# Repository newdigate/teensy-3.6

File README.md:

# Teensy 3.6 audio display projects

I'd like to explore whats possible with a teensy 3.6, the sgtl5000 audioboard, and an ILI9341 tft display board;
* https://www.pjrc.com/teensy/index.html
* https://www.pjrc.com/store/teensy3_audio.html
* https://www.pjrc.com/store/display_ili9341.html

I have a little bit of electrical engineering knowledge but I don't have alot of practical experience. I am a software engineer by trade and Im interested in audio applications of the teensy devices; 

I've wired the three components together using breadboard and jumper wires. Although it does work intermittently, the digital i2s audio connection is very fragile and mostly results in heavy digital distorion. I've tried to rule out all the obvious potential faults - swapped teensy mainboards, swapped audioboards, swapped different versions of teensy devices... the problem seems to be with my breadboard, or the jumper wires. I need to check it out with a decent oscilliscope. So I've decided to build a custom PCB. I think this should solve my distortion issue.    

[some things I learned about Fritzing](https://github.com/newdigate/teensy-3.6/tree/master/fritzing)

### About Teensy:
Teensy is an awesome microcontroller development kit from pjrc.com http://www.pjrc.com/teensy/index.html

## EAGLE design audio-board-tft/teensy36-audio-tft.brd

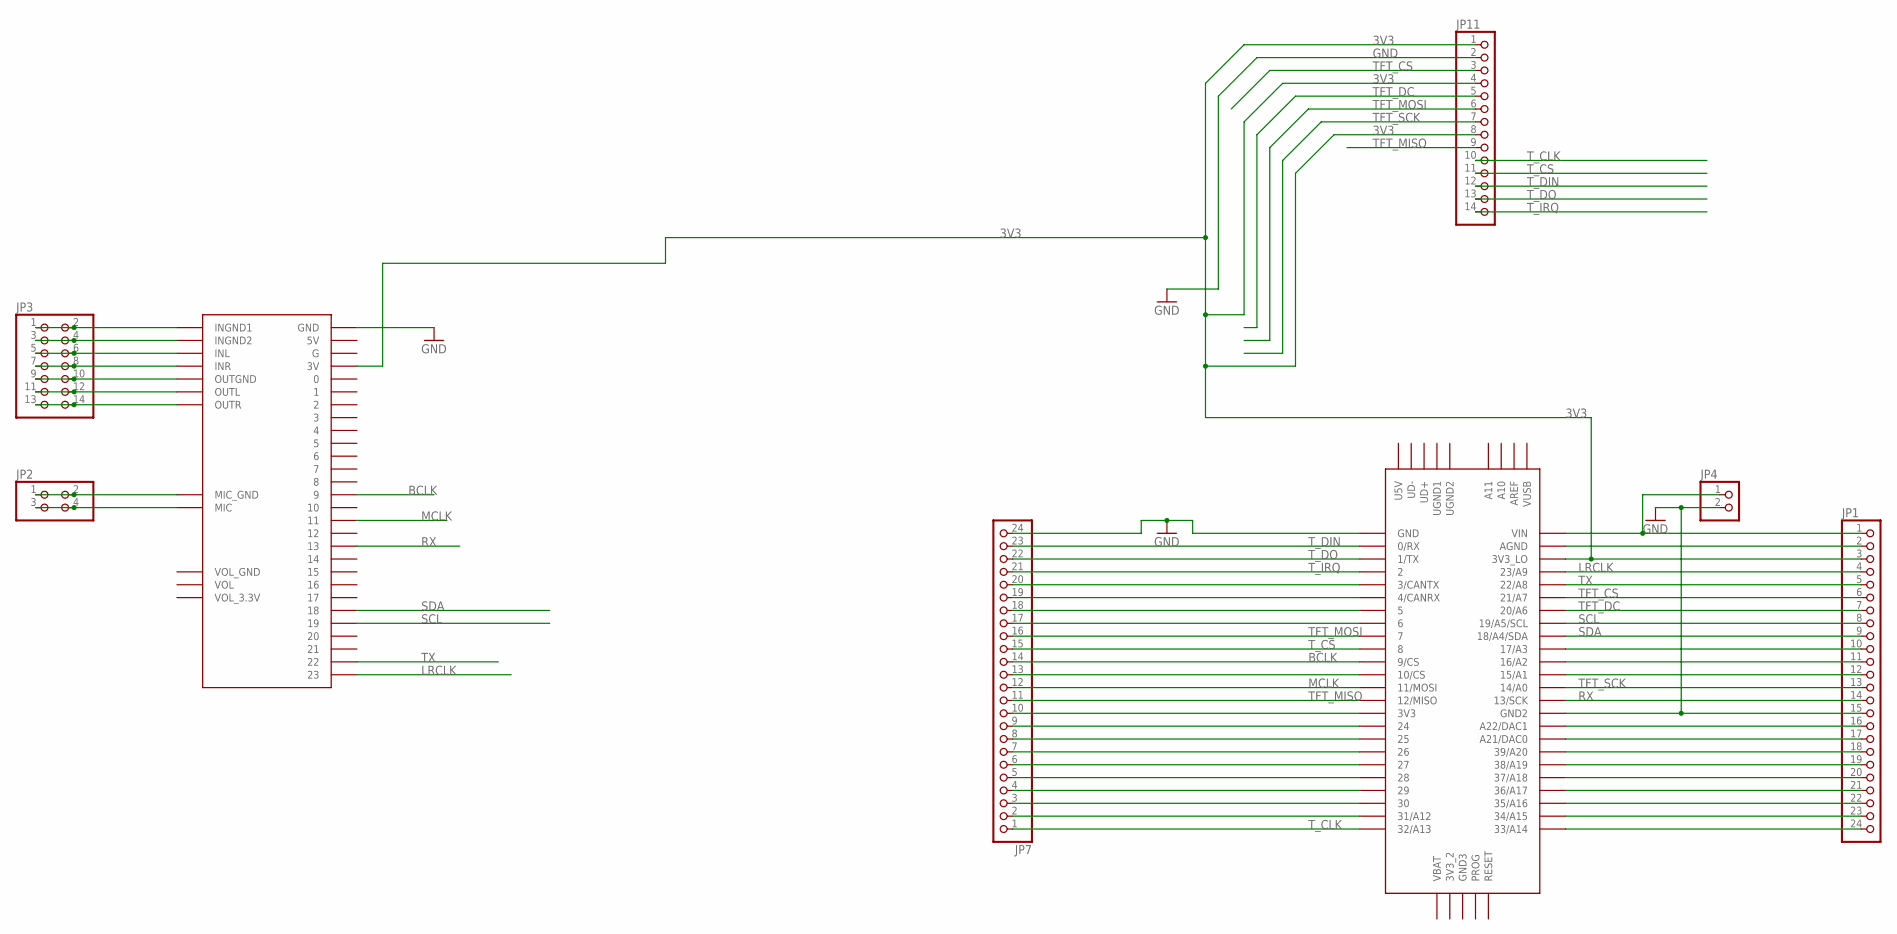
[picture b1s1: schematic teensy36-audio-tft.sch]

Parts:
JP1, JP7: PINHD-1X24; 1X24
JP2: PINHD-2X2; 2X02
JP3: PINHD-2X7; 2X07
JP4: PINHD-1X2; 1X02
JP11: PINHD-1X14; 1X14
U$2: AUDIOSHIELD
U$3: TEENSY_3.5/3.6

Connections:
3V3: JP1.3, JP11.1, JP11.4, JP11.8, U$2.3V, U$3.3V3_LO
BCLK: JP7.14, U$2.9, U$3.9/CS
GND: JP1.15, JP4.2, JP7.24, JP11.2, U$2.GND, U$3.GND, U$3.GND2
LRCLK: JP1.4, U$2.23, U$3.23/A9
MCLK: JP7.12, U$2.11, U$3.11/MOSI
unnamed: JP2.1, JP2.2, U$2.GND_MIC (MIC_GND)
unnamed: JP1.1, JP4.1, U$3.VIN
unnamed: JP7.20, U$3.3/CANTX
unnamed: JP7.19, U$3.4/CANRX
unnamed: JP7.18, U$3.5
unnamed: JP2.3, JP2.4, U$2.MIC
unnamed: JP3.1, JP3.2, U$2.INGND1
unnamed: JP3.3, JP3.4, U$2.INGND2
unnamed: JP3.5, JP3.6, U$2.INL
unnamed: JP3.7, JP3.8, U$2.INR
unnamed: JP3.9, JP3.10, U$2.OUTGND
unnamed: JP3.11, JP3.12, U$2.OUTL
unnamed: JP3.13, JP3.14, U$2.OUTR
unnamed: JP7.17, U$3.6
unnamed: JP7.13, U$3.10/CS
unnamed: JP7.10, U$3.3V3
unnamed: JP7.9, U$3.24
unnamed: JP7.8, U$3.25
unnamed: JP7.7, U$3.26
unnamed: JP7.6, U$3.27
unnamed: JP7.5, U$3.28
unnamed: JP7.4, U$3.29
unnamed: JP7.3, U$3.30
unnamed: JP7.2, U$3.31/A12
unnamed: JP1.2, U$3.AGND
unnamed: JP1.10, U$3.17/A3
unnamed: JP1.11, U$3.16/A2
unnamed: JP1.12, U$3.15/A1
unnamed: JP1.16, U$3.A22/DAC1
unnamed: JP1.17, U$3.21/DAC0 (A21/DAC0)
unnamed: JP1.18, U$3.39/A20
unnamed: JP1.19, U$3.38/A19
unnamed: JP1.20, U$3.37/A18
unnamed: JP1.21, U$3.36/A17
unnamed: JP1.22, U$3.35/A16
unnamed: JP1.23, U$3.34/A15
unnamed: JP1.24, U$3.33/A14
RX: JP1.14, U$2.13, U$3.13/SCK
SCL: JP1.8, U$2.19, U$3.19/A5/SCL
SDA: JP1.9, U$2.18, U$3.18/A4/SDA
TFT_CS: JP1.6, JP11.3, U$3.21/A7
TFT_DC: JP1.7, JP11.5, U$3.20/A6
TFT_MISO: JP7.11, JP11.9
TFT_MOSI: JP7.16, JP11.6, U$3.7
TFT_SCK: JP1.13, JP11.7, U$3.14/A0
TX: JP1.5, U$2.22, U$3.22/A8
T_CLK: JP7.1, JP11.10, U$3.32/A13
T_CS: JP7.15, JP11.11, U$3.8
T_DIN: JP7.23, JP11.12, U$3.0/RX
T_DO: JP7.22, JP11.13, U$3.1/TX
T_IRQ: JP7.21, JP11.14, U$3.2

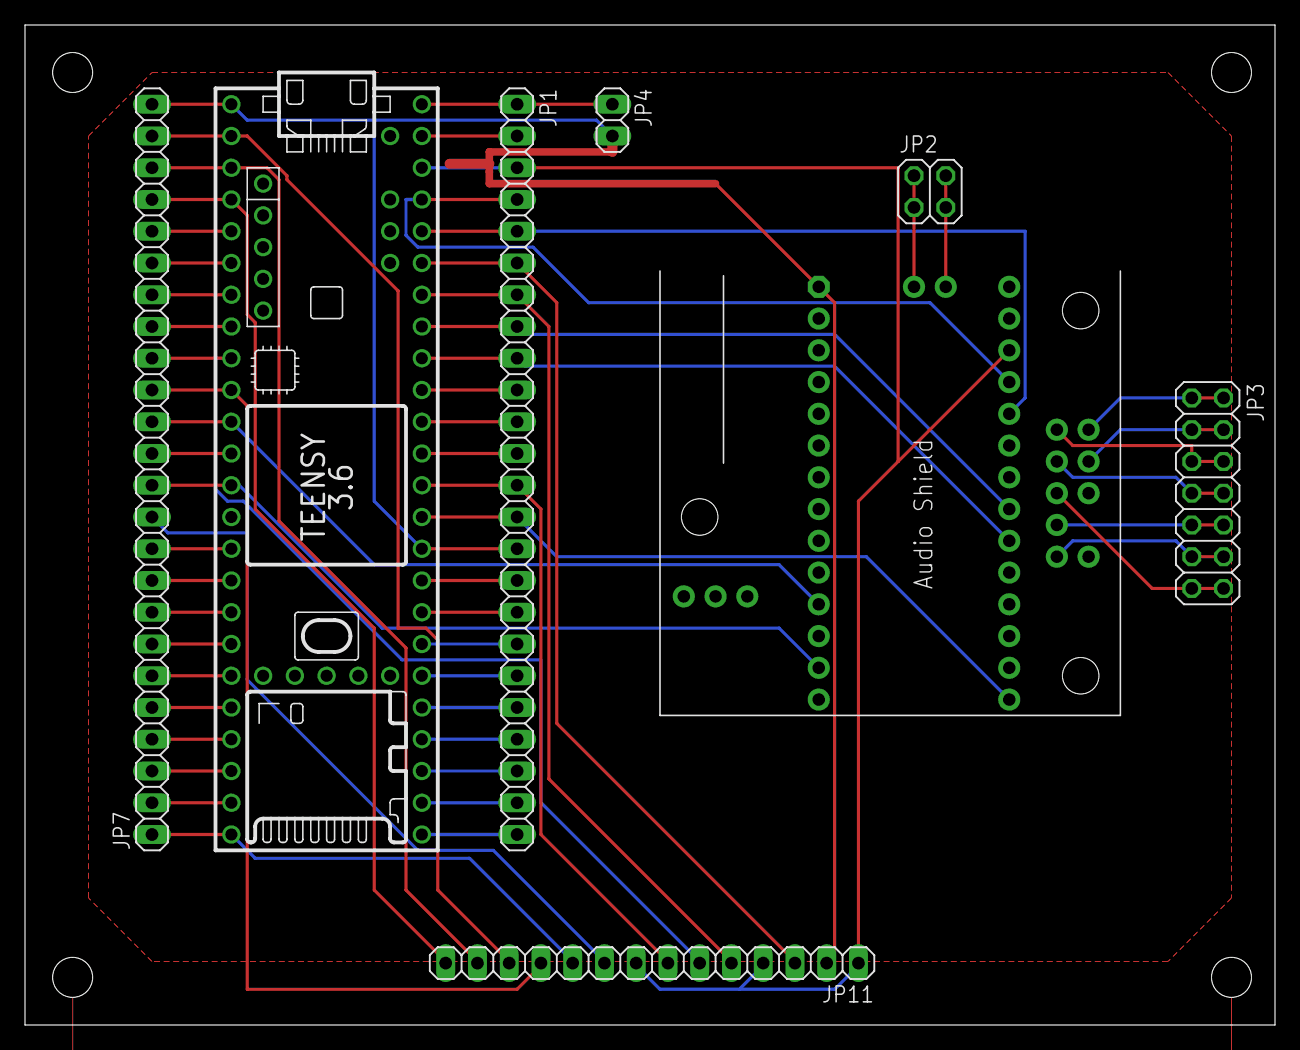
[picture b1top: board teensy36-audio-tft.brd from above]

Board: 2 copper layers, 100.0 x 80.0 mm, 8 parts (0 on the bottom side), 56 nets.

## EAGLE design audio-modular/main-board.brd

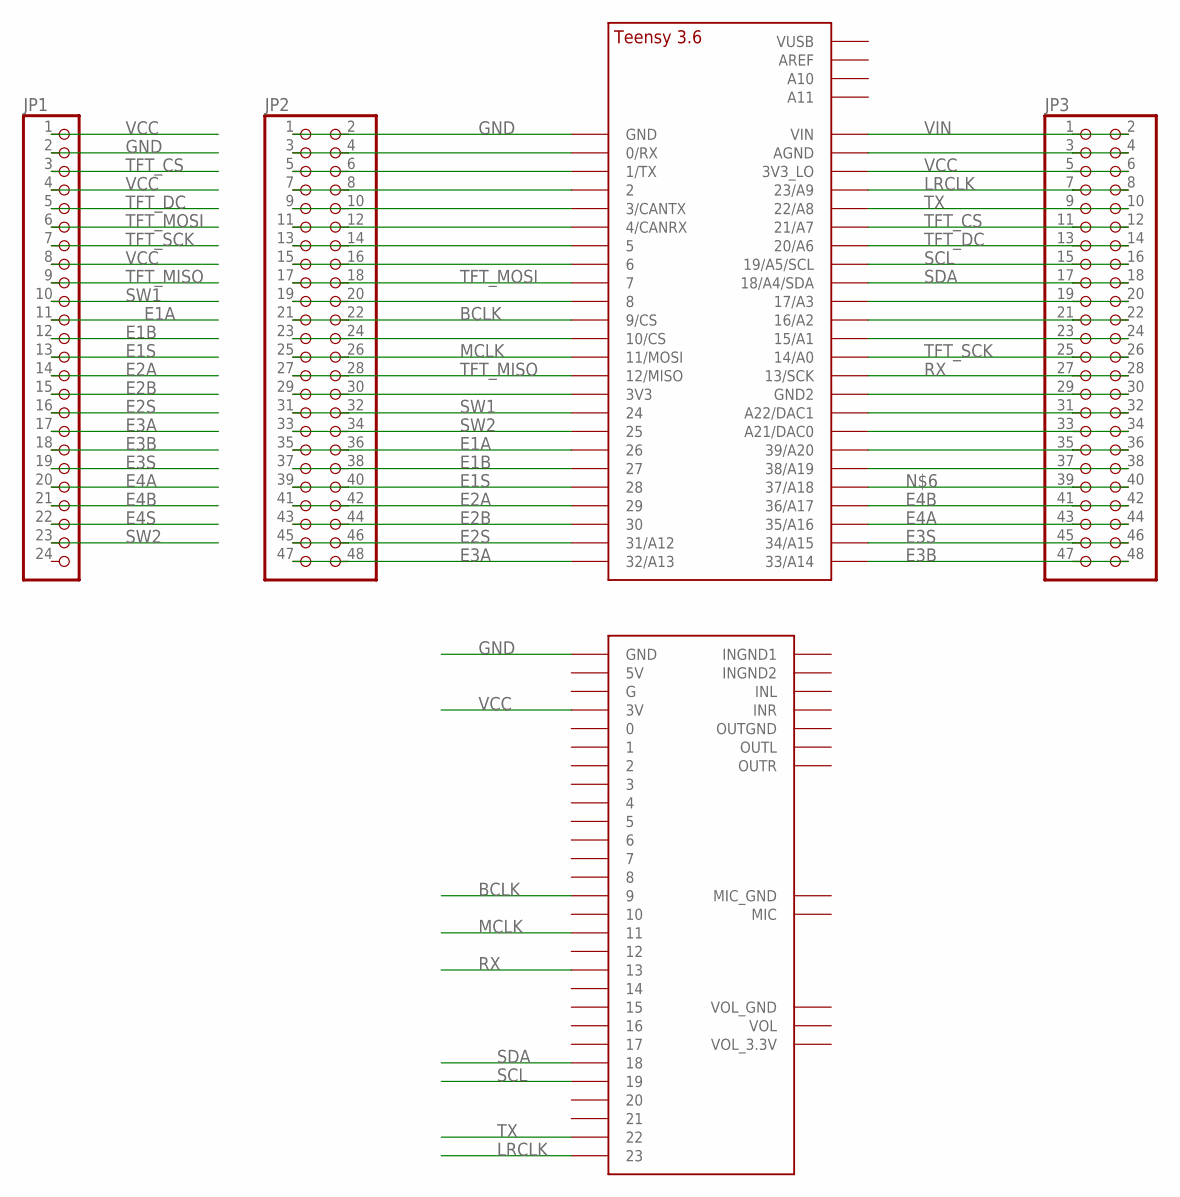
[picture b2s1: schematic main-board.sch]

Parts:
JP1: PINHD-1X24; 1X24
JP2, JP3: PINHD-2X24; 2X24
U$1: TEENSY_3.5/3.6_BASIC
U$2: AUDIOSHIELD

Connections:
BCLK: JP2.21, JP2.22, U$1.9/CS, U$2.9
E1A: JP1.11, JP2.35, JP2.36, U$1.26
E1B: JP1.12, JP2.37, JP2.38, U$1.27
E1S: JP1.13, JP2.39, JP2.40, U$1.28
E2A: JP1.14, JP2.41, JP2.42, U$1.29
E2B: JP1.15, JP2.43, JP2.44, U$1.30
E2S: JP1.16, JP2.45, JP2.46, U$1.31/A12
E3A: JP1.17, JP2.47, JP2.48, U$1.32/A13
E3B: JP1.18, JP3.47, JP3.48, U$1.33/A14
E3S: JP1.19, JP3.45, JP3.46, U$1.34/A15
E4A: JP1.20, JP3.43, JP3.44, U$1.35/A16
E4B: JP1.21, JP3.41, JP3.42, U$1.36/A17
E4S: JP1.22
GND: JP1.2, JP2.1, JP2.2, U$1.GND, U$2.GND
LRCLK: JP3.7, JP3.8, U$1.23/A9, U$2.23
MCLK: JP2.25, JP2.26, U$1.11/MOSI, U$2.11
unnamed: JP2.3, JP2.4, U$1.0/RX
unnamed: JP2.5, JP2.6, U$1.1/TX
unnamed: JP2.7, JP2.8, U$1.2
unnamed: JP3.39, JP3.40, U$1.37/A18
unnamed: JP2.9, JP2.10, U$1.3/CANTX
unnamed: JP2.11, JP2.12, U$1.4/CANRX
unnamed: JP2.13, JP2.14, U$1.5
unnamed: JP2.15, JP2.16, U$1.6
unnamed: JP2.19, JP2.20, U$1.8
unnamed: JP2.23, JP2.24, U$1.10/CS
unnamed: JP2.29, JP2.30, U$1.3V3
unnamed: JP3.3, JP3.4, U$1.AGND
unnamed: JP3.19, JP3.20, U$1.17/A3
unnamed: JP3.21, JP3.22, U$1.16/A2
unnamed: JP3.23, JP3.24, U$1.15/A1
unnamed: JP3.29, JP3.30, U$1.GND2
unnamed: JP3.31, JP3.32, U$1.A22/DAC1
unnamed: JP3.33, JP3.34, U$1.21/DAC0 (A21/DAC0)
unnamed: JP3.35, JP3.36, U$1.39/A20
unnamed: JP3.37, JP3.38, U$1.38/A19
RX: JP3.27, JP3.28, U$1.13/SCK, U$2.13
SCL: JP3.15, JP3.16, U$1.19/A5/SCL, U$2.19
SDA: JP3.17, JP3.18, U$1.18/A4/SDA, U$2.18
SW1: JP1.10, JP2.31, JP2.32, U$1.24
SW2: JP1.23, JP2.33, JP2.34, U$1.25
TFT_CS: JP1.3, JP3.11, JP3.12, U$1.21/A7
TFT_DC: JP1.5, JP3.13, JP3.14, U$1.20/A6
TFT_MISO: JP1.9, JP2.27, JP2.28, U$1.12/MISO
TFT_MOSI: JP1.6, JP2.17, JP2.18, U$1.7
TFT_SCK: JP1.7, JP3.25, JP3.26, U$1.14/A0
TX: JP3.9, JP3.10, U$1.22/A8, U$2.22
VCC: JP1.1, JP1.4, JP1.8, JP3.5, JP3.6, U$1.3V3_LO, U$2.3V
VIN: JP3.1, JP3.2, U$1.VIN

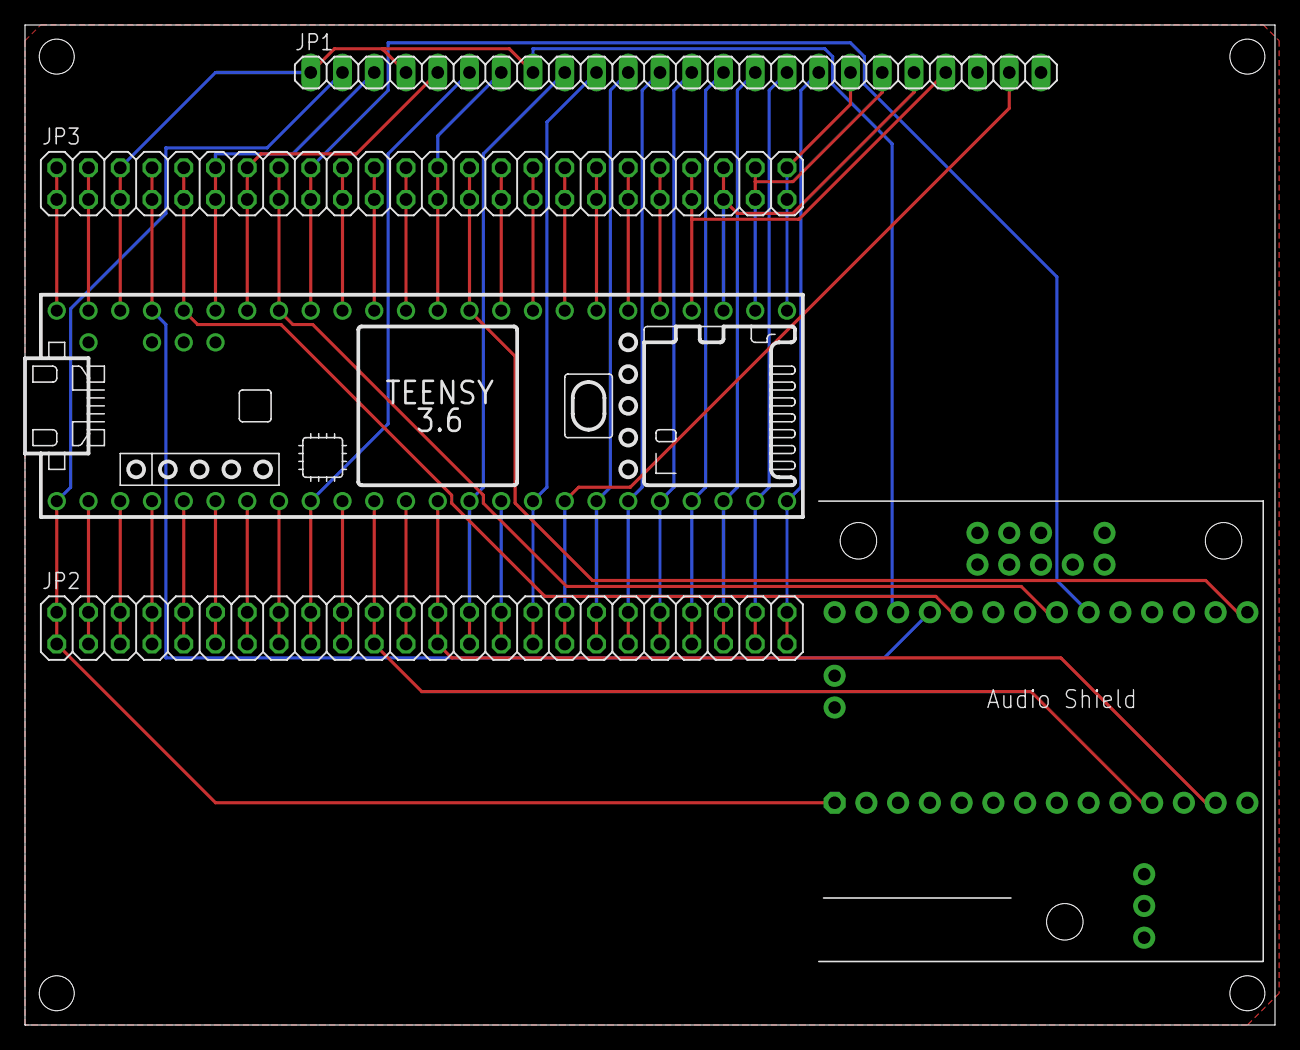
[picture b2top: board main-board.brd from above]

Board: 2 copper layers, 100.0 x 80.0 mm, 5 parts (0 on the bottom side), 48 nets.

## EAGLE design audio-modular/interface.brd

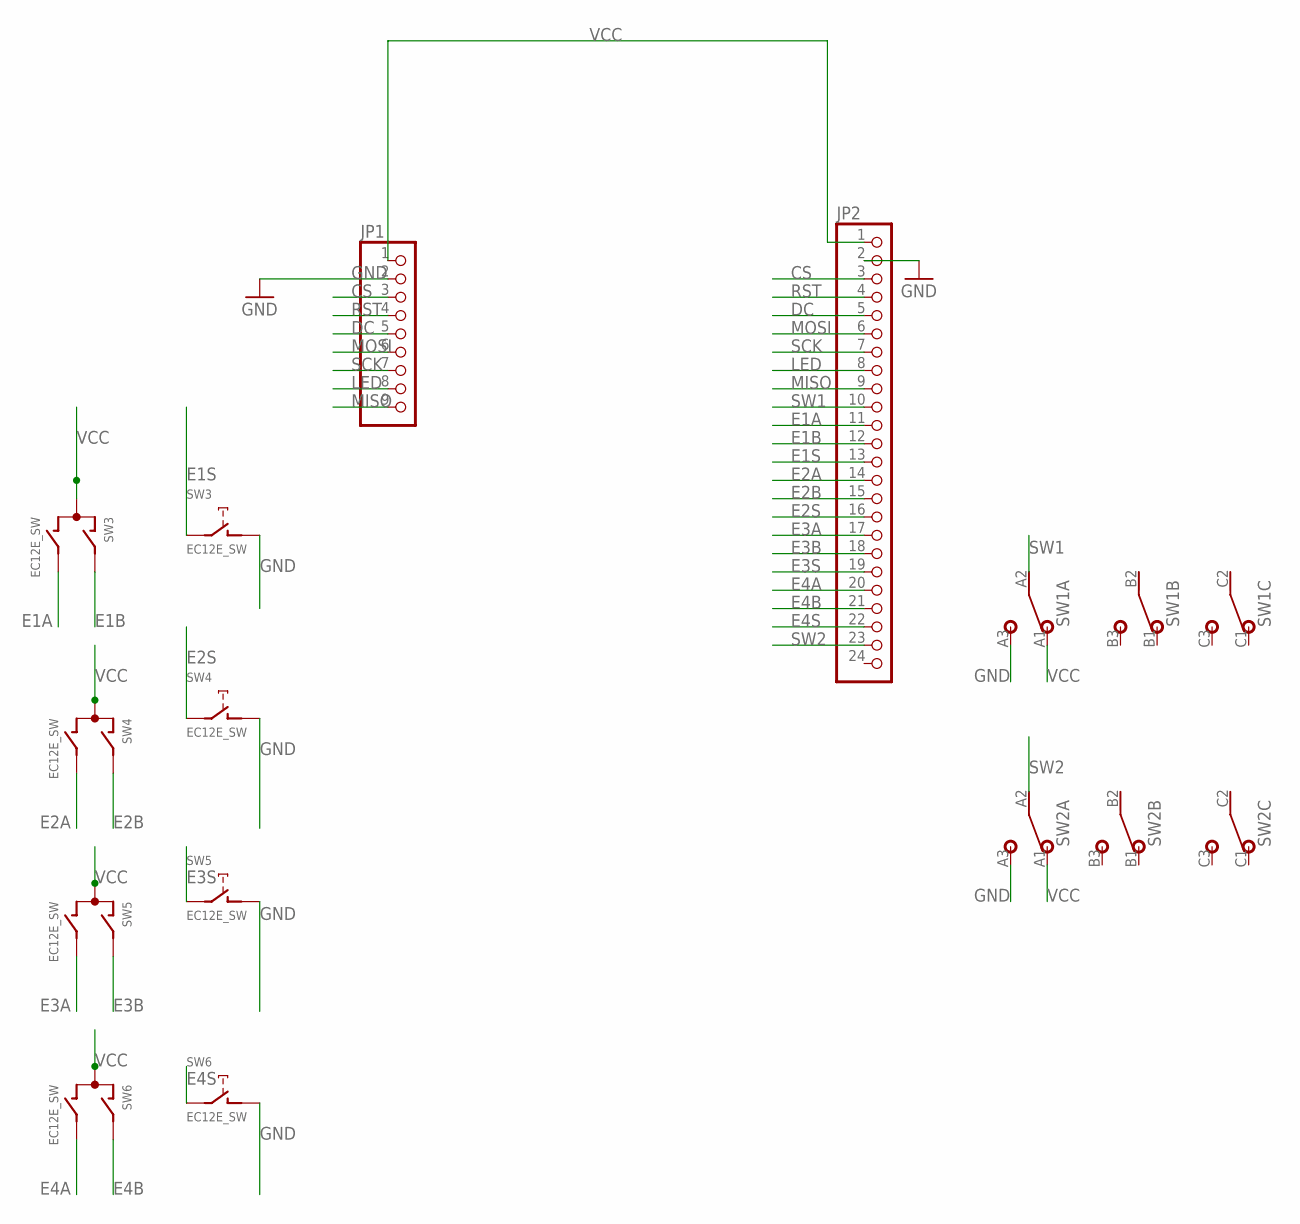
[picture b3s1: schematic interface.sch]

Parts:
JP1: PINHD-1X9; 1X09
JP2: PINHD-1X24; 1X24
SW1, SW2: 3PDTBLUE; CHINABLUE
SW3, SW4, SW5, SW6: EC12E_SW; ALPS_EC12E_SW

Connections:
CS: JP1.3, JP2.3
DC: JP1.5, JP2.5
E1A: JP2.11, SW3.B
E1B: JP2.12, SW3.A
E1S: JP2.13, SW3.E (2)
E2A: JP2.14, SW4.B
E2B: JP2.15, SW4.A
E2S: JP2.16, SW4.E (2)
E3A: JP2.17, SW5.B
E3B: JP2.18, SW5.A
E3S: JP2.19, SW5.E (2)
E4A: JP2.20, SW6.B
E4B: JP2.21, SW6.A
E4S: JP2.22, SW6.E (2)
GND: JP1.2, JP2.2, SW1.A3 (3), SW2.A3 (3), SW3.D (1), SW4.D (1), SW5.D (1), SW6.D (1)
LED: JP1.8, JP2.8
MISO: JP1.9, JP2.9
MOSI: JP1.6, JP2.6
RST: JP1.4, JP2.4
SCK: JP1.7, JP2.7
SW1: JP2.10, SW1.A2 (2)
SW2: JP2.23, SW2.A2 (2)
VCC: JP1.1, JP2.1, SW1.A1 (1), SW2.A1 (1), SW3.C, SW4.C, SW5.C, SW6.C

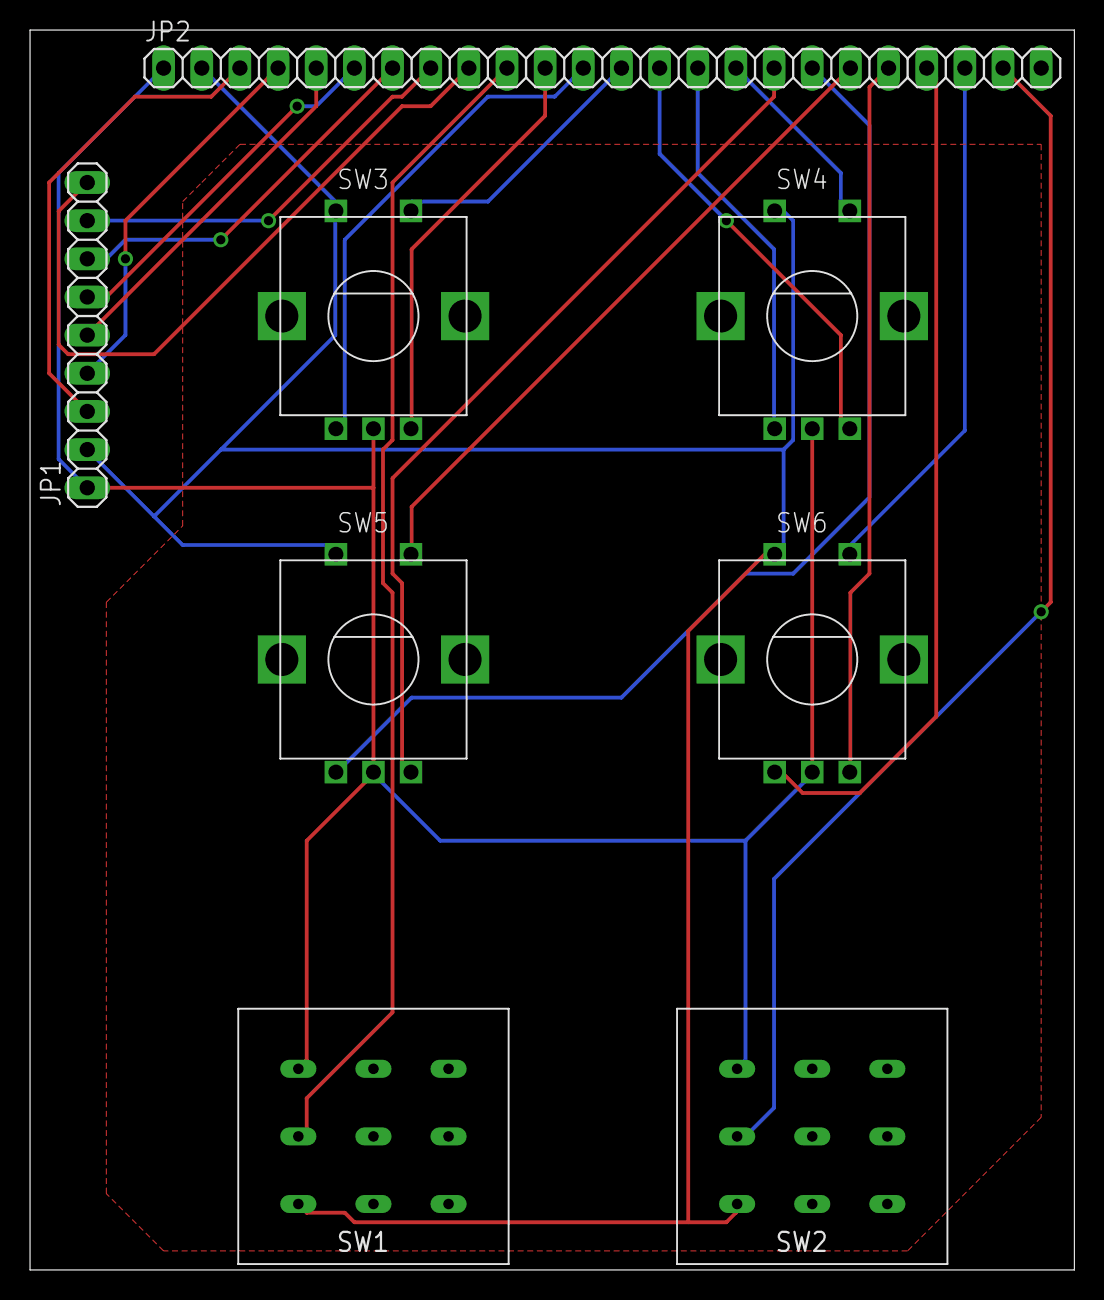
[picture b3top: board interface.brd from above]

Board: 2 copper layers, 69.5 x 82.5 mm, 8 parts (0 on the bottom side), 23 nets.

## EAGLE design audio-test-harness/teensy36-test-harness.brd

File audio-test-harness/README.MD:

Circuit, PCB and sketches for Teensy audio display test harness

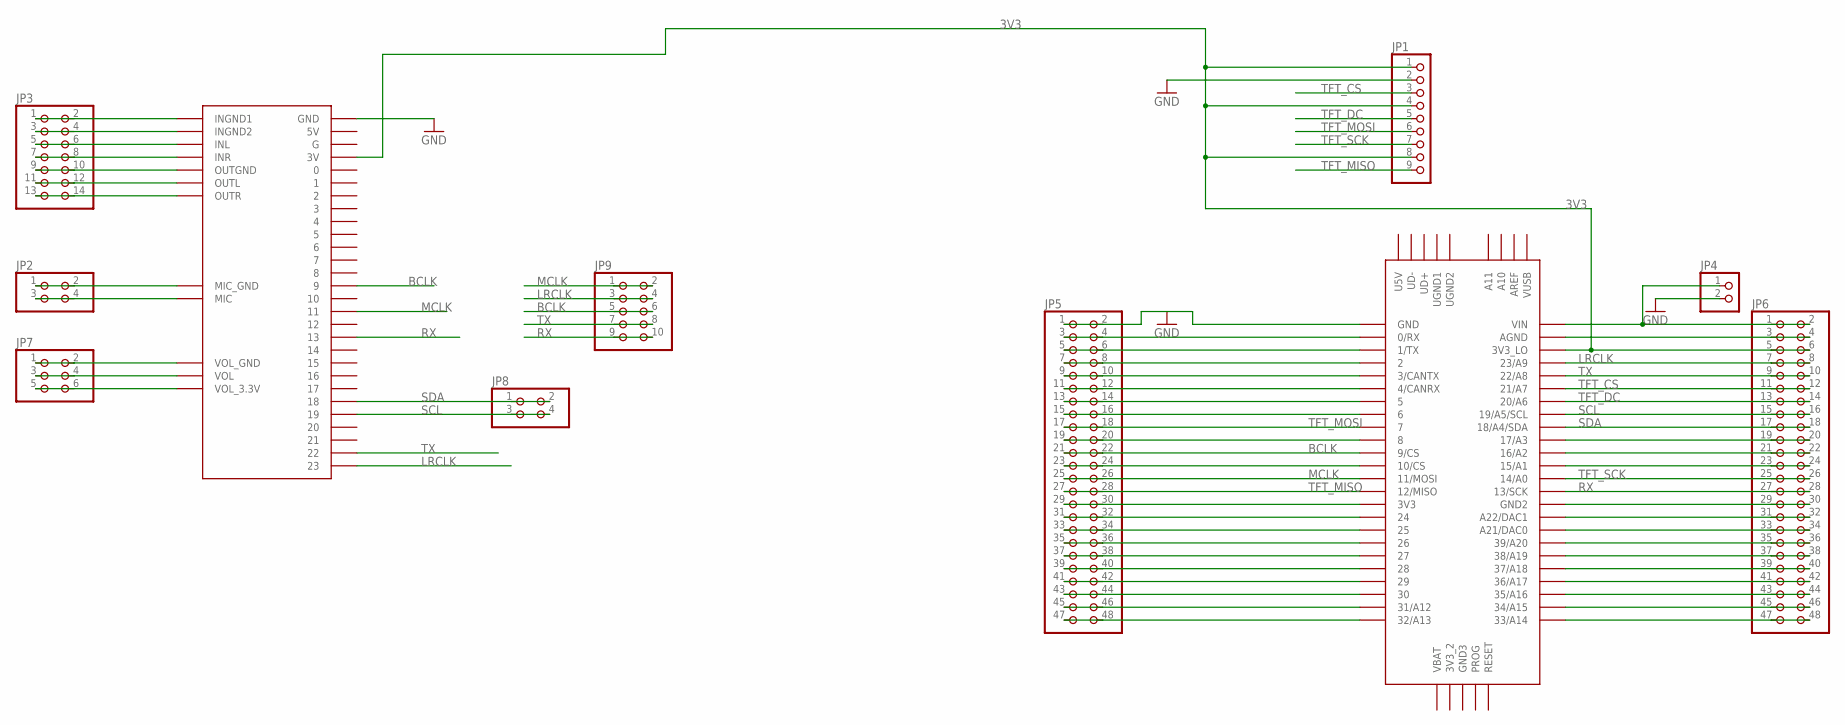
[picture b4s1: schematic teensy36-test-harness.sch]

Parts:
JP1: PINHD-1X9; 1X09
JP2, JP8: PINHD-2X2; 2X02
JP3: PINHD-2X7; 2X07
JP4: PINHD-1X2; 1X02
JP5, JP6: PINHD-2X24; 2X24
JP7: PINHD-2X3; 2X03
JP9: PINHD-2X5; 2X05
U$2: AUDIOSHIELD
U$3: TEENSY_3.5/3.6

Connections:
3V3: JP1.1, JP1.4, JP1.8, JP6.5, JP6.6, U$2.3V, U$3.3V3_LO
BCLK: JP5.21, JP5.22, JP9.5, JP9.6, U$2.9, U$3.9/CS
GND: JP1.2, JP4.2, JP5.1, JP5.2, U$2.GND, U$3.GND
LRCLK: JP6.7, JP6.8, JP9.3, JP9.4, U$2.23, U$3.23/A9
MCLK: JP5.25, JP5.26, JP9.1, JP9.2, U$2.11, U$3.11/MOSI
unnamed: JP2.1, JP2.2, U$2.GND_MIC (MIC_GND)
unnamed: JP4.1, JP6.1, JP6.2, U$3.VIN
unnamed: JP7.1, JP7.2, U$2.VOL_GND
unnamed: JP5.3, JP5.4, U$3.0/RX
unnamed: JP5.5, JP5.6, U$3.1/TX
unnamed: JP5.7, JP5.8, U$3.2
unnamed: JP5.9, JP5.10, U$3.3/CANTX
unnamed: JP5.11, JP5.12, U$3.4/CANRX
unnamed: JP5.13, JP5.14, U$3.5
unnamed: JP2.3, JP2.4, U$2.MIC
unnamed: JP3.1, JP3.2, U$2.INGND1
unnamed: JP3.3, JP3.4, U$2.INGND2
unnamed: JP3.5, JP3.6, U$2.INL
unnamed: JP3.7, JP3.8, U$2.INR
unnamed: JP3.9, JP3.10, U$2.OUTGND
unnamed: JP3.11, JP3.12, U$2.OUTL
unnamed: JP3.13, JP3.14, U$2.OUTR
unnamed: JP5.15, JP5.16, U$3.6
unnamed: JP7.3, JP7.4, U$2.VOL
unnamed: JP5.19, JP5.20, U$3.8
unnamed: JP7.5, JP7.6, U$2.VOL_3.3V
unnamed: JP5.23, JP5.24, U$3.10/CS
unnamed: JP5.29, JP5.30, U$3.3V3
unnamed: JP5.31, JP5.32, U$3.24
unnamed: JP5.33, JP5.34, U$3.25
unnamed: JP5.35, JP5.36, U$3.26
unnamed: JP5.37, JP5.38, U$3.27
unnamed: JP5.39, JP5.40, U$3.28
unnamed: JP5.41, JP5.42, U$3.29
unnamed: JP5.43, JP5.44, U$3.30
unnamed: JP5.45, JP5.46, U$3.31/A12
unnamed: JP5.47, JP5.48, U$3.32/A13
unnamed: JP6.3, JP6.4, U$3.AGND
unnamed: JP6.19, JP6.20, U$3.17/A3
unnamed: JP6.21, JP6.22, U$3.16/A2
unnamed: JP6.23, JP6.24, U$3.15/A1
unnamed: JP6.29, JP6.30, U$3.GND2
unnamed: JP6.31, JP6.32, U$3.A22/DAC1
unnamed: JP6.33, JP6.34, U$3.21/DAC0 (A21/DAC0)
unnamed: JP6.35, JP6.36, U$3.39/A20
unnamed: JP6.37, JP6.38, U$3.38/A19
unnamed: JP6.39, JP6.40, U$3.37/A18
unnamed: JP6.41, JP6.42, U$3.36/A17
unnamed: JP6.43, JP6.44, U$3.35/A16
unnamed: JP6.45, JP6.46, U$3.34/A15
unnamed: JP6.47, JP6.48, U$3.33/A14
RX: JP6.27, JP6.28, JP9.9, JP9.10, U$2.13, U$3.13/SCK
SCL: JP6.15, JP6.16, JP8.3, JP8.4, U$2.19, U$3.19/A5/SCL
SDA: JP6.17, JP6.18, JP8.1, JP8.2, U$2.18, U$3.18/A4/SDA
TFT_CS: JP1.3, JP6.11, JP6.12, U$3.21/A7
TFT_DC: JP1.5, JP6.13, JP6.14, U$3.20/A6
TFT_MISO: JP1.9, JP5.27, JP5.28
TFT_MOSI: JP1.6, JP5.17, JP5.18, U$3.7
TFT_SCK: JP1.7, JP6.25, JP6.26, U$3.14/A0
TX: JP6.9, JP6.10, JP9.7, JP9.8, U$2.22, U$3.22/A8

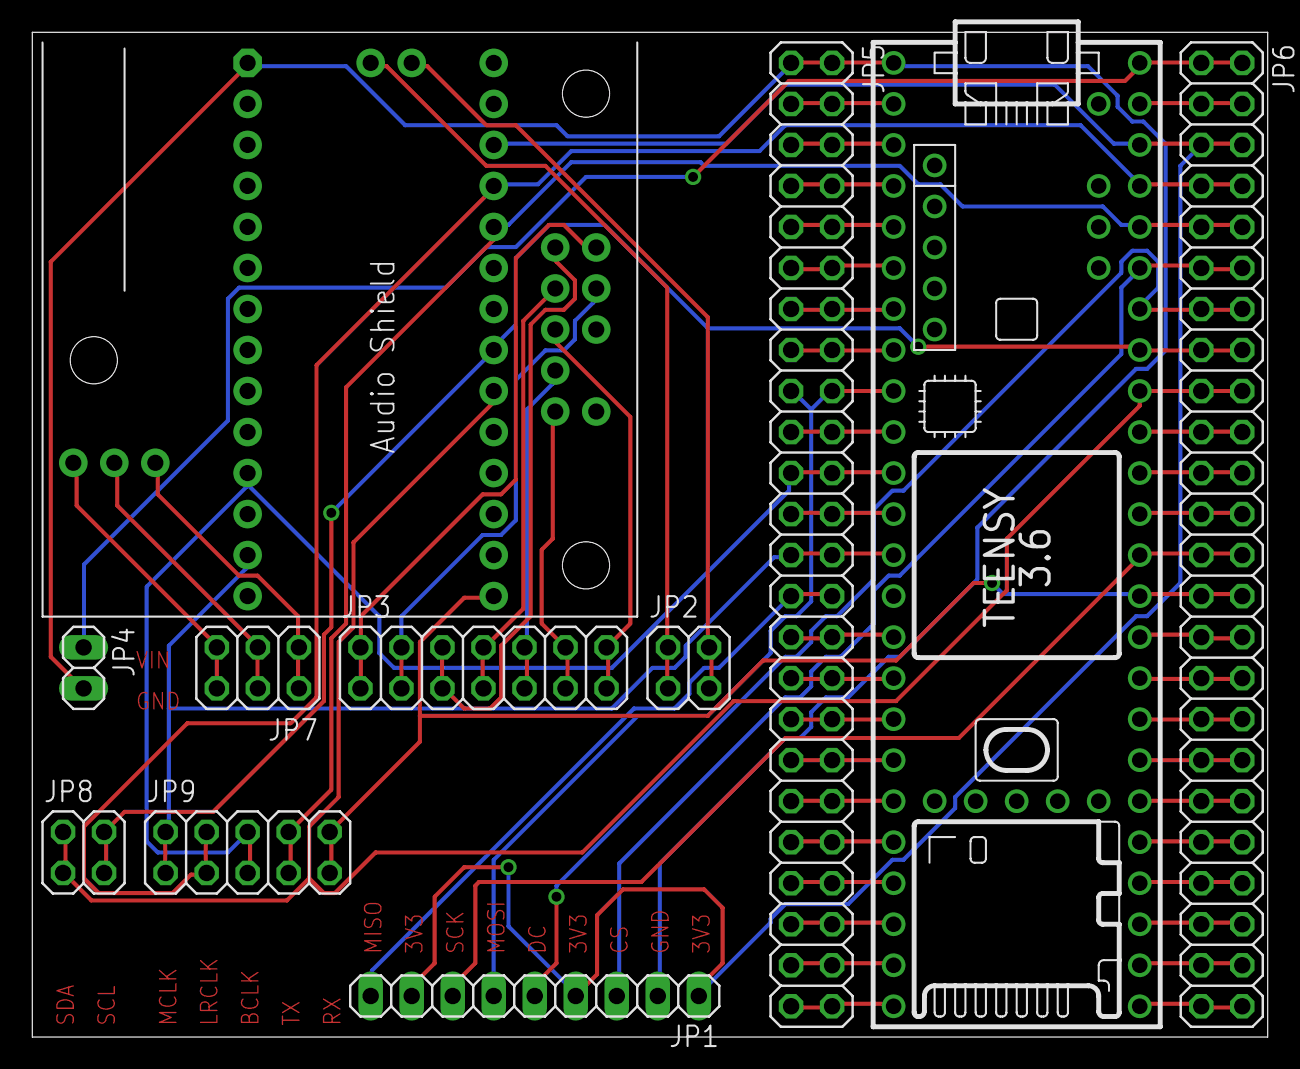
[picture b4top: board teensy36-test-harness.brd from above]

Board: 2 copper layers, 76.5 x 62.2 mm, 11 parts (0 on the bottom side), 60 nets.

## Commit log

2017-01-02 Rename audio-test-harness/README.MD to audio-test-harness/eagle/README.MD
2017-01-02 moved eagle libraries to common folder
2017-01-07 cleanup
2017-01-07 clean up
